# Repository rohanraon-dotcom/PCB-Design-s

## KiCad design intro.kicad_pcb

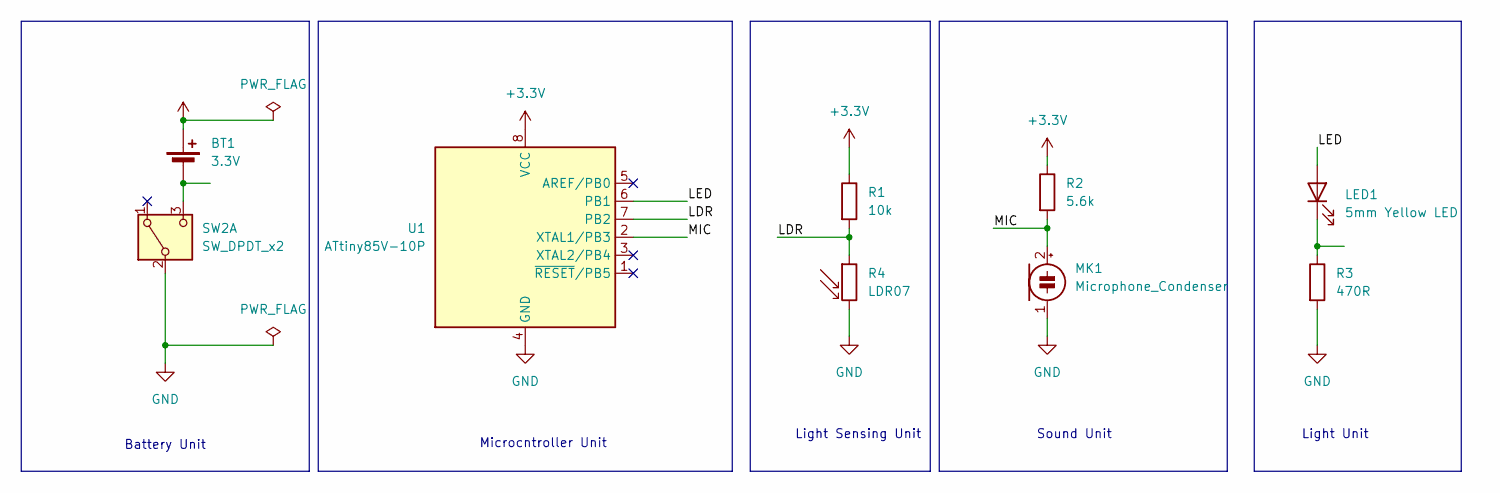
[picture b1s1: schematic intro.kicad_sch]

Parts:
BT1: 3.3V; BatteryHolder_ComfortableElectronic_CH273-2450_1x2450
LED1: 5mm Yellow LED; LED_D5.0mm
MK1: Microphone_Condenser; PinHeader_1x02_P2.54mm_Vertical
R1: 10k; R_Axial_DIN0207_L6.3mm_D2.5mm_P15.24mm_Horizontal
R2: 5.6k; R_Axial_DIN0207_L6.3mm_D2.5mm_P15.24mm_Horizontal
R3: 470R; R_Axial_DIN0207_L6.3mm_D2.5mm_P15.24mm_Horizontal
R4: LDR07; R_LDR_5.1x4.3mm_P3.4mm_Vertical
SW2: SW_DPDT_x2; SW_Slide_SPDT_Angled_CK_OS102011MA1Q
U1: ATtiny85V-10P; DIP-8_W7.62mm

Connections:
+3.3V: BT1.1 (+), R1.1, R2.1, U1.8 (VCC)
/LDR: R1.2, R4.1, U1.7 (PB2)
/LED: LED1.2 (A), U1.6 (PB1)
/MIC: MK1.2 (+), R2.2, U1.2 (XTAL1/PB3)
GND: MK1.1 (-), R3.2, R4.2, SW2.2 (B), U1.4 (GND)
unnamed: BT1.2 (-), SW2.3 (C)
unnamed: LED1.1 (K), R3.1

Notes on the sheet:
Light Unit
Microcntroller Unit
Light Sensing Unit
Battery Unit
Sound Unit

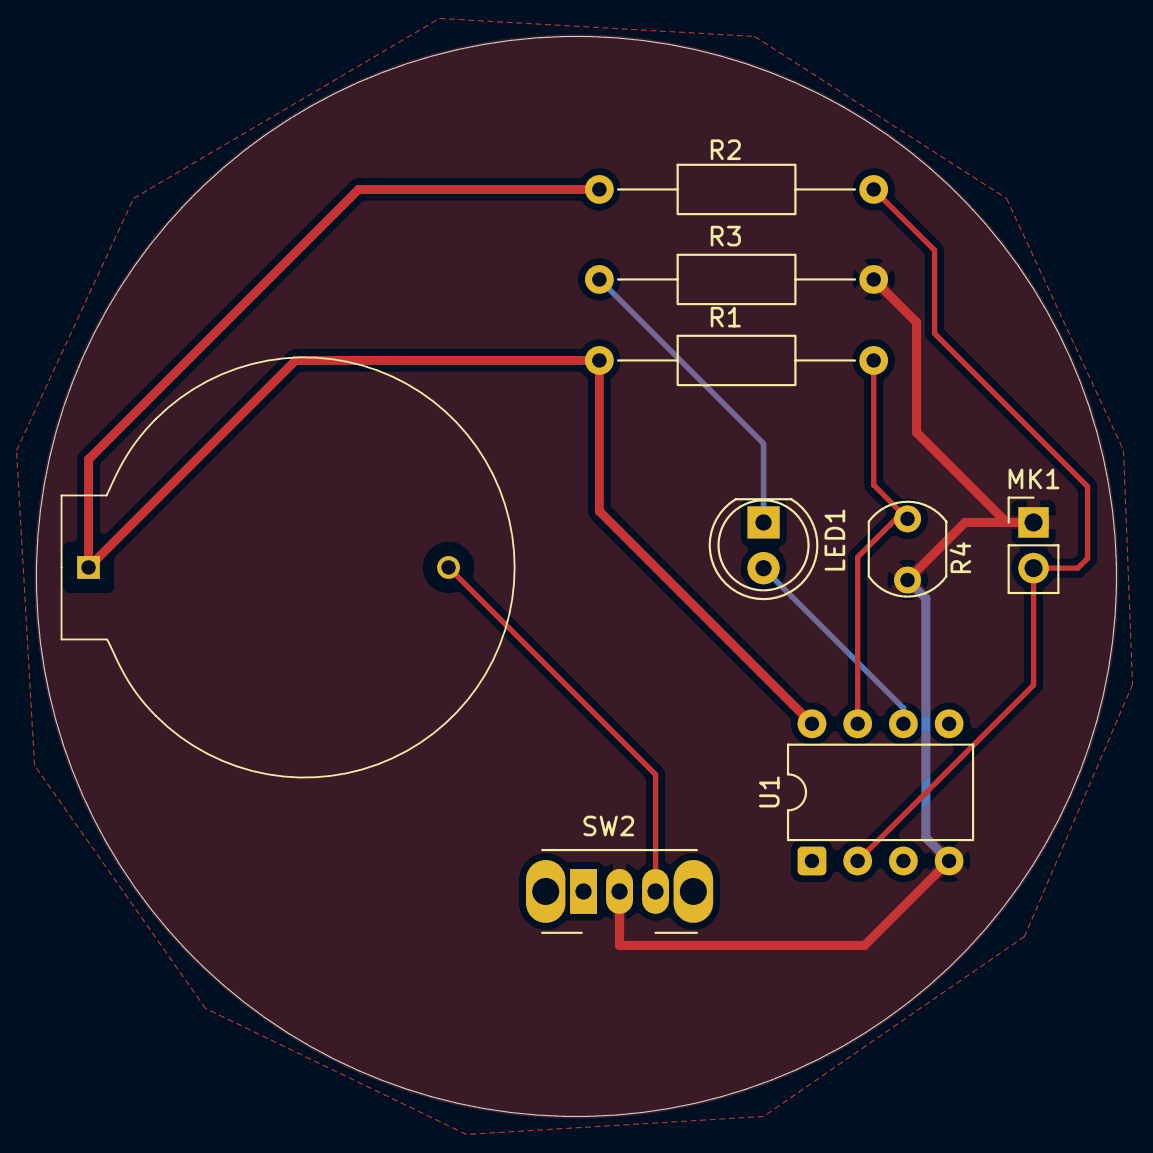
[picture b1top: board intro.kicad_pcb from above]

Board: 2 copper layers, 60.0 x 60.0 mm, 9 parts (0 on the bottom side), 7 nets.

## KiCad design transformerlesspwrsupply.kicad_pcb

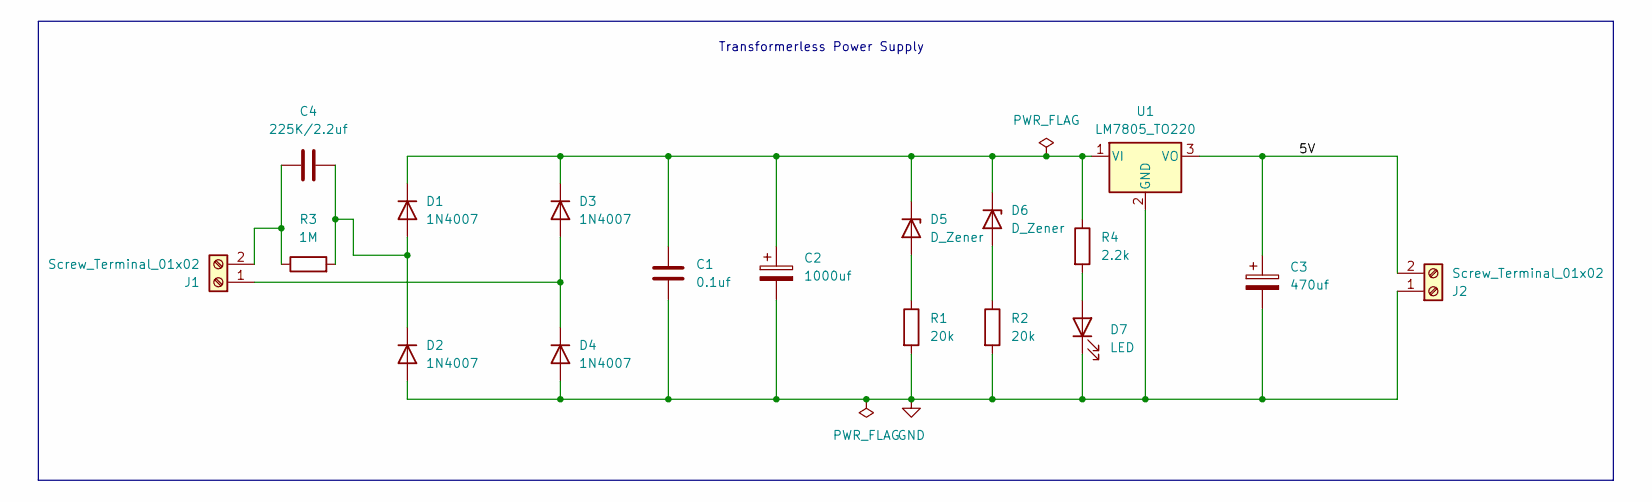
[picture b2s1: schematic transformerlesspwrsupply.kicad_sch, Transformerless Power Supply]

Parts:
C1: 0.1uf; C_Disc_D4.7mm_W2.5mm_P5.00mm
C2: 1000uf; CP_Radial_D10.0mm_P5.00mm
C3: 470uf; CP_Radial_D10.0mm_P3.80mm
C4: 225K/2.2uf; C_Rect_L18.0mm_W6.0mm_P15.00mm_FKS3_FKP3
D1, D2, D3, D4: 1N4007; D_DO-41_SOD81_P10.16mm_Horizontal
D5, D6: D_Zener; D_A-405_P7.62mm_Horizontal
D7: LED; LED_D5.0mm
J1, J2: Screw_Terminal_01x02; TerminalBlock_4Ucon_1x02_P3.50mm_Horizontal
R1, R2: 20k; R_Axial_DIN0207_L6.3mm_D2.5mm_P10.16mm_Horizontal
R3: 1M; R_Axial_DIN0207_L6.3mm_D2.5mm_P10.16mm_Horizontal
R4: 2.2k; R_Axial_DIN0207_L6.3mm_D2.5mm_P10.16mm_Horizontal
U1: LM7805_TO220; TO-220-3_Vertical

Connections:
/5V: C3.1, J2.2, U1.3 (VO)
GND: C1.2, C2.2, C3.2, D2.2 (A), D4.2 (A), D7.1 (K), J2.1, R1.2, R2.2, U1.2 (GND)
unnamed: C4.2, D1.2 (A), D2.1 (K), R3.2
unnamed: C1.1, C2.1, D1.1 (K), D3.1 (K), D5.1 (K), D6.1 (K), R4.1, U1.1 (VI)
unnamed: D3.2 (A), D4.1 (K), J1.1
unnamed: D5.2 (A), R1.1
unnamed: D6.2 (A), R2.1
unnamed: D7.2 (A), R4.2
unnamed: C4.1, J1.2, R3.1

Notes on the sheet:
Transformerless Power Supply

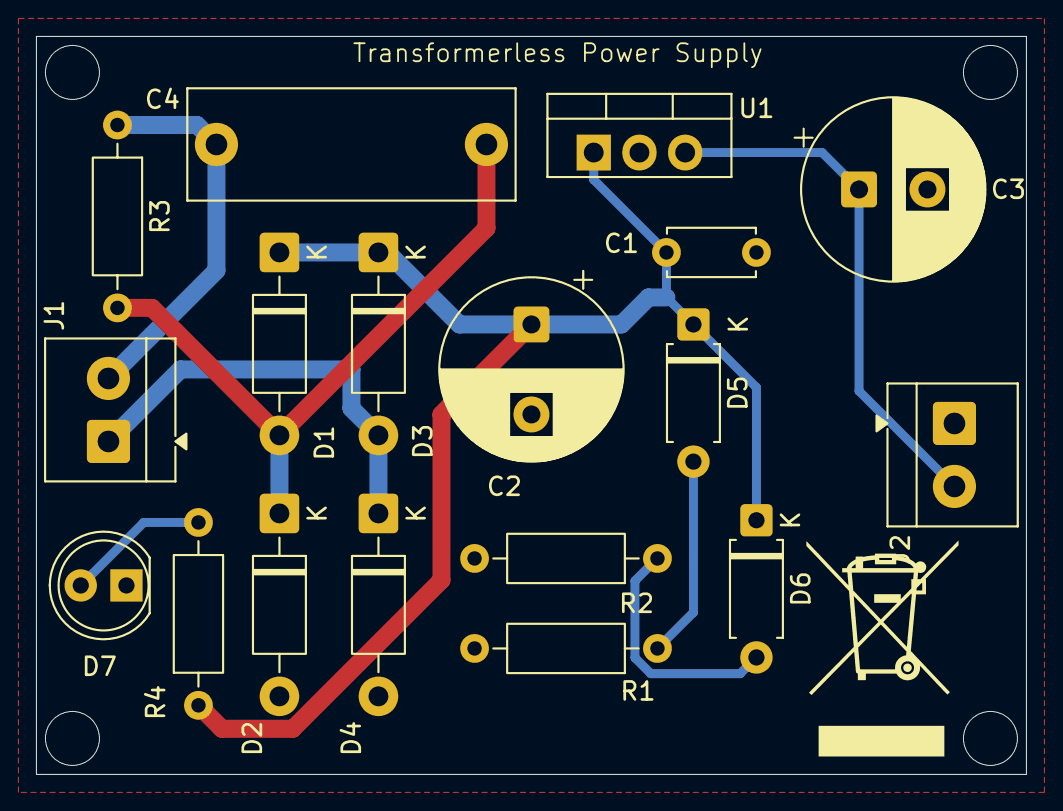
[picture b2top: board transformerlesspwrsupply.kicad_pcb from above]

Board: 2 copper layers, 55.0 x 41.0 mm, 18 parts (0 on the bottom side), 9 nets.

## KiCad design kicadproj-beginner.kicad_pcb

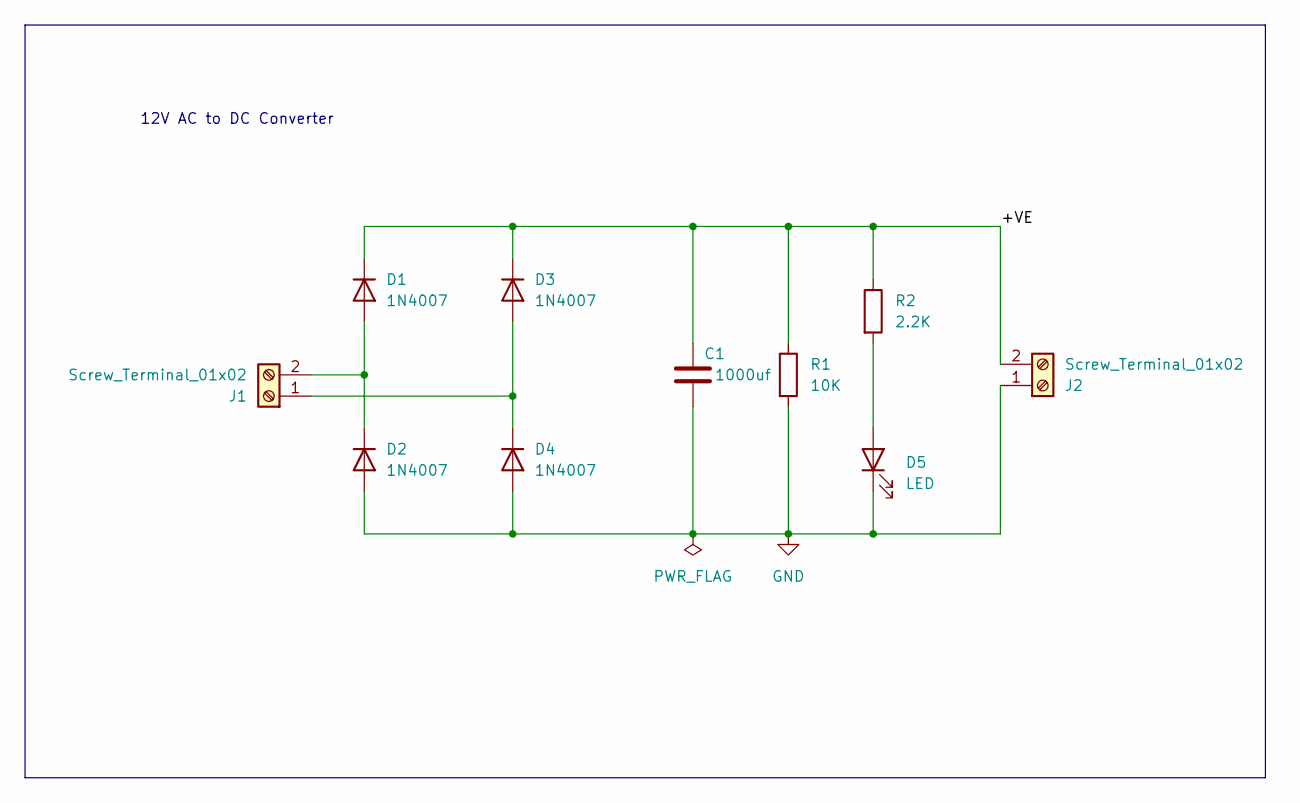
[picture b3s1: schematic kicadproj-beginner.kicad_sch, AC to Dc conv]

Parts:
C1: 1000uf; C_Radial_D8.0mm_H11.5mm_P3.50mm
D1, D2, D3, D4: 1N4007; D_DO-41_SOD81_P10.16mm_Horizontal
D5: LED; LED_D5.0mm
J1, J2: Screw_Terminal_01x02; TerminalBlock_CUI_TB007-508-02_1x02_P5.08mm_Horizontal
R1: 10K; R_Axial_DIN0204_L3.6mm_D1.6mm_P7.62mm_Horizontal
R2: 2.2K; R_Axial_DIN0204_L3.6mm_D1.6mm_P7.62mm_Horizontal

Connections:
/+VE: C1.1, D1.1 (K), D3.1 (K), J2.2, R1.1, R2.1
GND: C1.2, D2.2 (A), D4.2 (A), D5.1 (K), J2.1, R1.2
unnamed: D1.2 (A), D2.1 (K), J1.2
unnamed: D3.2 (A), D4.1 (K), J1.1
unnamed: D5.2 (A), R2.2

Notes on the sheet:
12V AC to DC Converter

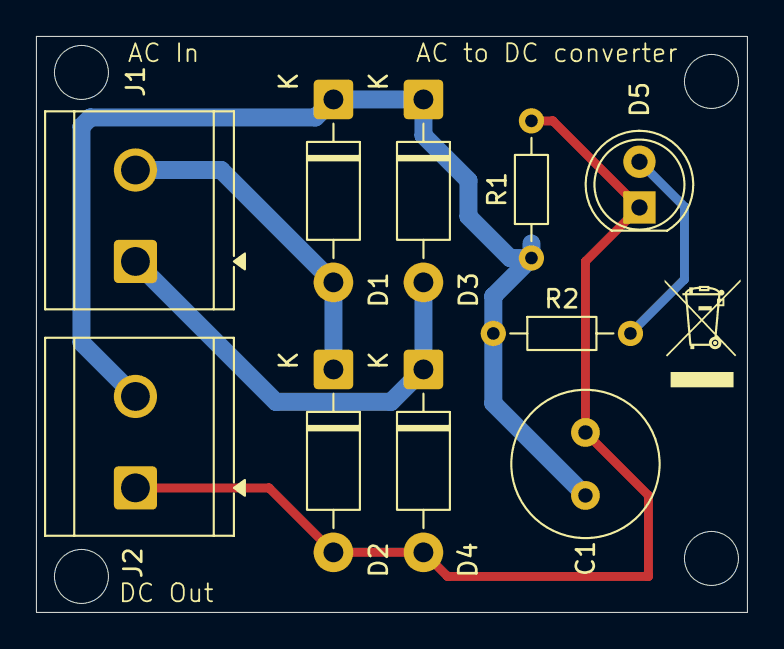
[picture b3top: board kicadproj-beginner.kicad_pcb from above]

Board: 2 copper layers, 39.5 x 32.0 mm, 10 parts (0 on the bottom side), 5 nets.
